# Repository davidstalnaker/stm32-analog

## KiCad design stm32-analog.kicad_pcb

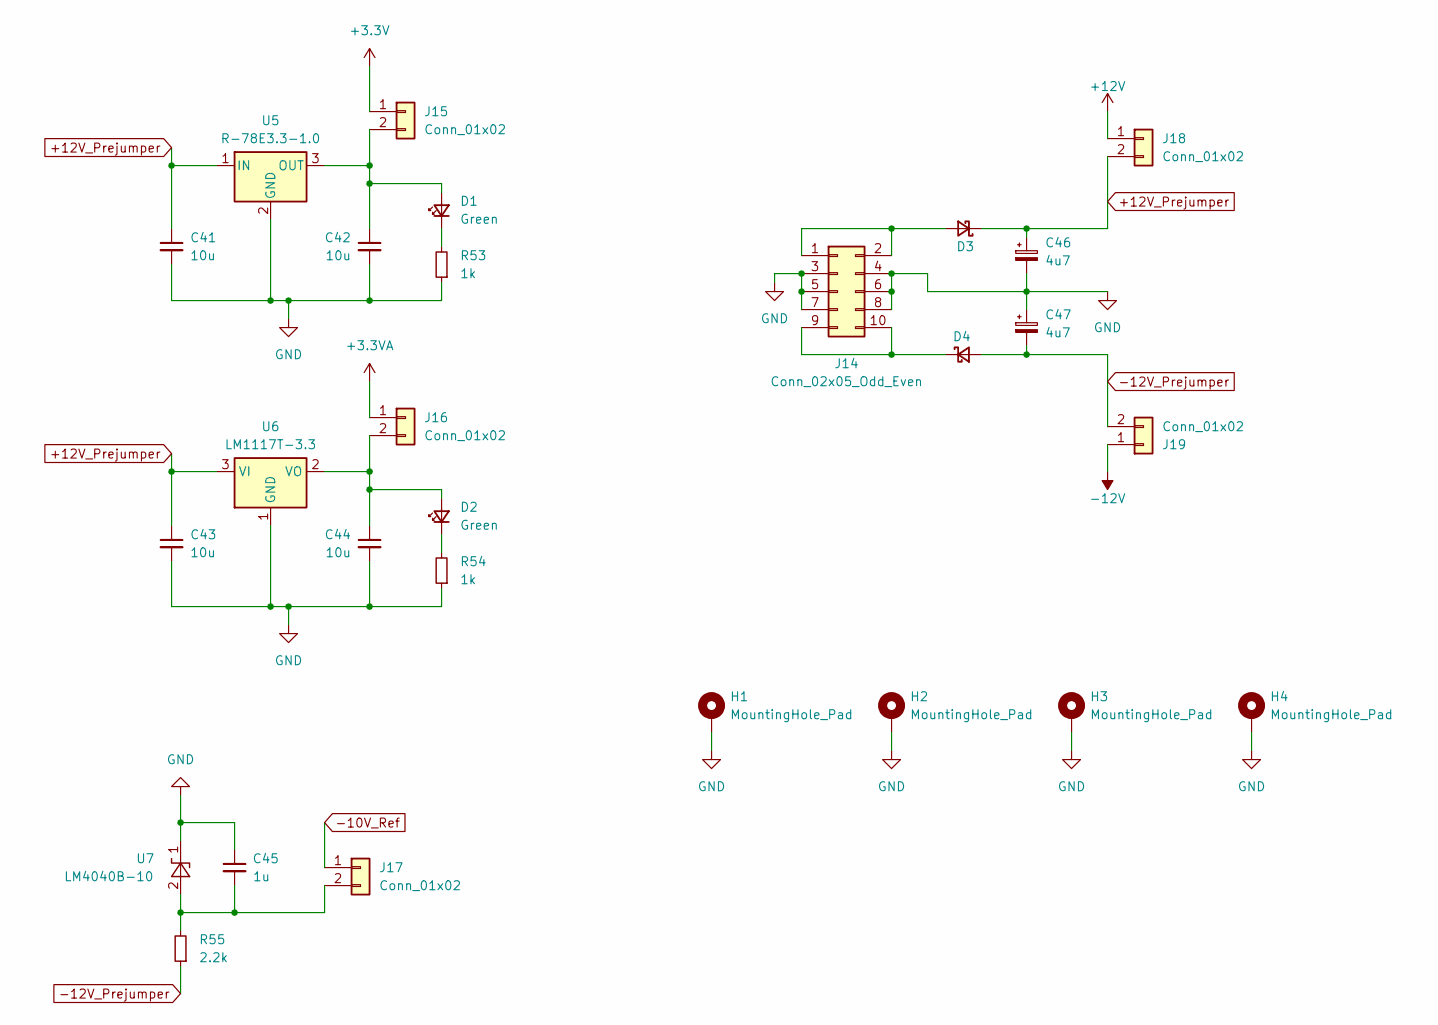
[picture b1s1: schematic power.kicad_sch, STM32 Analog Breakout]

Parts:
C41, C42, C43, C44: 10u; C_0805_2012Metric_Pad1.18x1.45mm_HandSolder
C45: 1u; C_0805_2012Metric_Pad1.18x1.45mm_HandSolder
C46, C47: 4u7; CP_Elec_4x3
D1, D2: Green; LED_0805_2012Metric_Pad1.15x1.40mm_HandSolder
D3, D4: D_Schottky_Small; D_SOD-323_HandSoldering
H1, H2, H3, H4: MountingHole_Pad; MountingHole_3.2mm_M3_DIN965_Pad
J14: Conn_02x05_Odd_Even; PinSocket_2x05_P2.54mm_Vertical
J15, J16, J17, J18, J19: Conn_01x02; PinSocket_1x02_P2.54mm_Vertical
R53, R54: 1k; R_0805_2012Metric_Pad1.20x1.40mm_HandSolder
R55: 2.2k; R_0805_2012Metric_Pad1.20x1.40mm_HandSolder
U5: R-78E3.3-1.0; Converter_DCDC_RECOM_R-78E-0.5_THT
U6: LM1117T-3.3; TO-220-3_Vertical
U7: LM4040B-10; SOT-23

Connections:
+3.3V: J15.1; also elsewhere on the board
+3.3VA: J16.1; also elsewhere on the board
+12V: J18.1; also elsewhere on the board
+12V_Prejumper: C41.1, C43.1, C46.1, D3.1 (K), J18.2, U5.1 (IN), U6.3 (VI)
-10V_Ref: J17.1; also elsewhere on the board
-12V: J19.1; also elsewhere on the board
-12V_Prejumper: C47.2, D4.2 (A), J19.2, R55.1
GND: C41.2, C42.2, C43.2, C44.2, C45.1, C46.2, C47.1, H1.1, H2.1, H3.1, H4.1, J14.3, J14.4, J14.5, J14.6, J14.7, J14.8, R53.1, R54.1, U5.2 (GND), U6.1 (GND), U7.1 (K); also elsewhere on the board
unnamed: C42.1, D1.2 (A), J15.2, U5.3 (OUT)
unnamed: D1.1 (K), R53.2
unnamed: C44.1, D2.2 (A), J16.2, U6.2 (VO)
unnamed: D2.1 (K), R54.2
unnamed: D3.2 (A), J14.1, J14.2
unnamed: D4.1 (K), J14.9, J14.10
unnamed: C45.2, J17.2, R55.2, U7.2 (A)

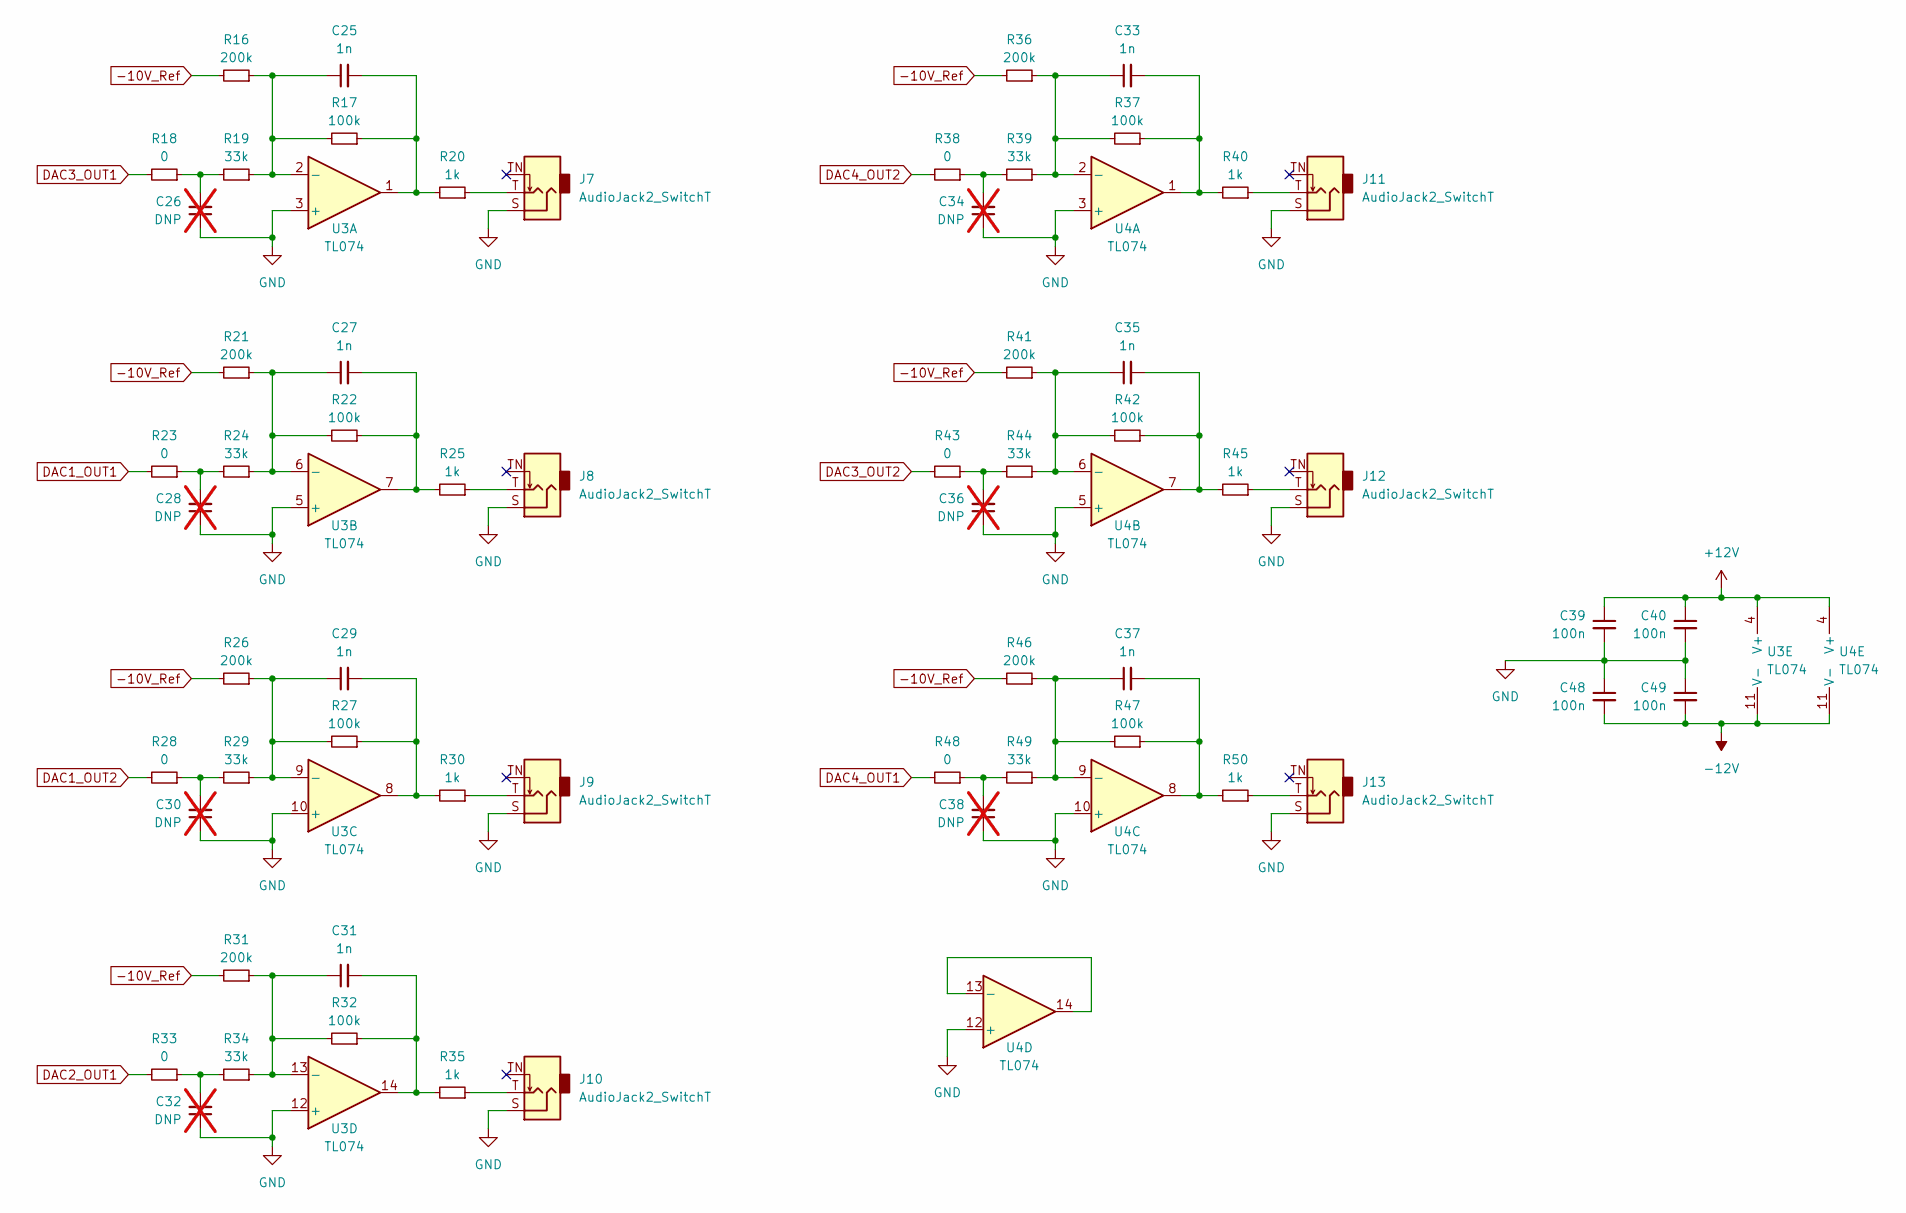
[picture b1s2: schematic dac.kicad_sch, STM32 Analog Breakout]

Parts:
C25, C27, C29, C31, C33, C35, C37: 1n; C_0805_2012Metric_Pad1.18x1.45mm_HandSolder
C26, C28, C30, C32, C34, C36, C38: DNP; C_0805_2012Metric_Pad1.18x1.45mm_HandSolder; not fitted
C39, C40, C48, C49: 100n; C_0805_2012Metric_Pad1.18x1.45mm_HandSolder
J7, J8, J9, J10, J11, J12, J13: AudioJack2_SwitchT; Jack_3.5mm_Thonkiconn_Tight
R16, R21, R26, R31, R36, R41, R46: 200k; R_0805_2012Metric_Pad1.20x1.40mm_HandSolder
R17, R22, R27, R32, R37, R42, R47: 100k; R_0805_2012Metric_Pad1.20x1.40mm_HandSolder
R18, R23, R28, R33, R38, R43, R48: 0; R_0805_2012Metric_Pad1.20x1.40mm_HandSolder
R19, R24, R29, R34, R39, R44, R49: 33k; R_0805_2012Metric_Pad1.20x1.40mm_HandSolder
R20, R25, R30, R35, R40, R45, R50: 1k; R_0805_2012Metric_Pad1.20x1.40mm_HandSolder
U3, U4: TL074; SOIC-14_3.9x8.7mm_P1.27mm

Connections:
+12V: C39.1, C40.1, U3.4 (V+), U4.4 (V+); also elsewhere on the board
-10V_Ref: R16.2, R21.2, R26.2, R31.2, R36.2, R41.2, R46.2; also elsewhere on the board
-12V: C48.2, C49.2, U3.11 (V-), U4.11 (V-); also elsewhere on the board
DAC1_OUT1: R23.2; also elsewhere on the board
DAC1_OUT2: R28.2; also elsewhere on the board
DAC2_OUT1: R33.2; also elsewhere on the board
DAC3_OUT1: R18.2; also elsewhere on the board
DAC3_OUT2: R43.2; also elsewhere on the board
DAC4_OUT1: R48.2; also elsewhere on the board
DAC4_OUT2: R38.2; also elsewhere on the board
GND: C26.1, C28.1, C30.1, C32.1, C34.1, C36.1, C38.1, C39.2, C40.2, C48.1, C49.1, J7.S, J8.S, J9.S, J10.S, J11.S, J12.S, J13.S, U3.3 (+), U3.5 (+), U3.10 (+), U3.12 (+), U4.3 (+), U4.5 (+), U4.10 (+), U4.12 (+); also elsewhere on the board
unnamed: C25.2, R17.1, R20.2, U3.1
unnamed: C26.2, R18.1, R19.2
unnamed: C27.2, R22.1, R25.2, U3.7
unnamed: C28.2, R23.1, R24.2
unnamed: C29.2, R27.1, R30.2, U3.8
unnamed: C30.2, R28.1, R29.2
unnamed: C31.2, R32.1, R35.2, U3.14
unnamed: C32.2, R33.1, R34.2
unnamed: C33.2, R37.1, R40.2, U4.1
unnamed: C34.2, R38.1, R39.2
unnamed: C35.2, R42.1, R45.2, U4.7
unnamed: C36.2, R43.1, R44.2
unnamed: C37.2, R47.1, R50.2, U4.8
unnamed: C38.2, R48.1, R49.2
unnamed: J7.T, R20.1
unnamed: J8.T, R25.1
unnamed: J9.T, R30.1
unnamed: J10.T, R35.1
unnamed: J11.T, R40.1
unnamed: J12.T, R45.1
unnamed: J13.T, R50.1
unnamed: C25.1, R16.1, R17.2, R19.1, U3.2 (-)
unnamed: C27.1, R21.1, R22.2, R24.1, U3.6 (-)
unnamed: C29.1, R26.1, R27.2, R29.1, U3.9 (-)
unnamed: C31.1, R31.1, R32.2, R34.1, U3.13 (-)
unnamed: C33.1, R36.1, R37.2, R39.1, U4.2 (-)
unnamed: C35.1, R41.1, R42.2, R44.1, U4.6 (-)
unnamed: C37.1, R46.1, R47.2, R49.1, U4.9 (-)
unnamed: U4.13 (-), U4.14

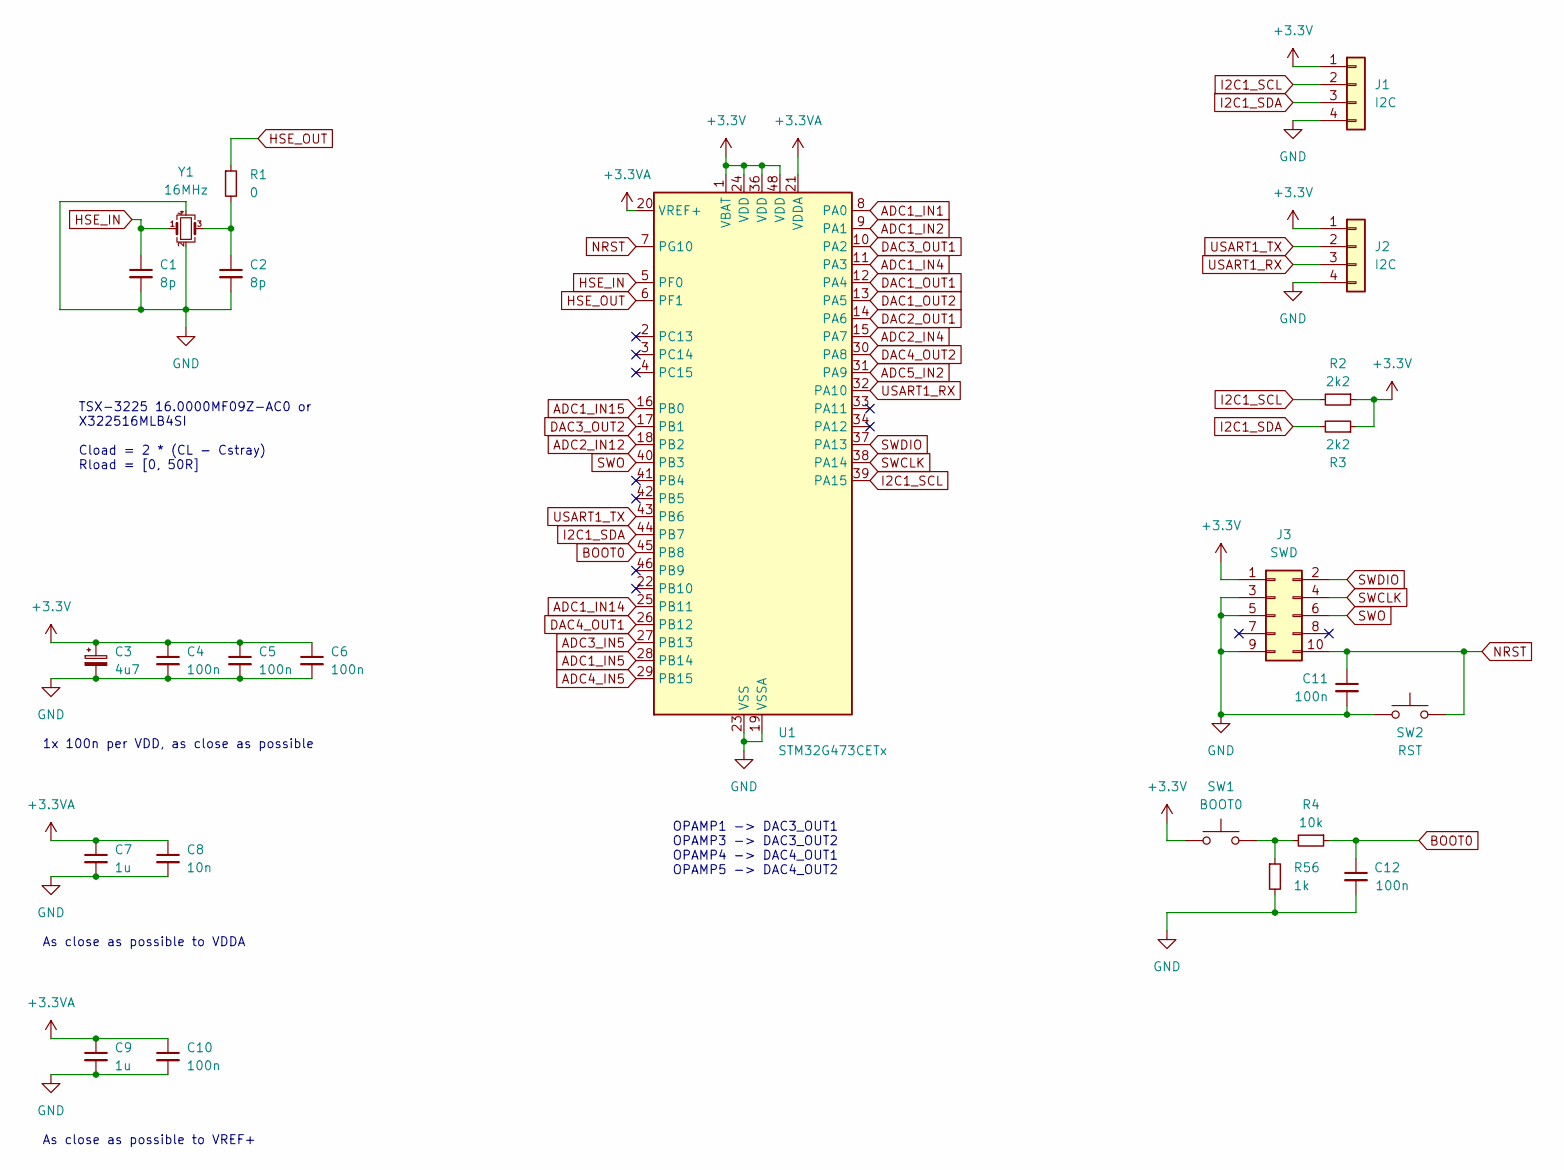
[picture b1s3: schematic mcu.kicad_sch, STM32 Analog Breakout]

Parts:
C1, C2: 8p; C_0805_2012Metric_Pad1.18x1.45mm_HandSolder
C3: 4u7; C_0805_2012Metric_Pad1.18x1.45mm_HandSolder
C4, C5, C6, C10, C11, C12: 100n; C_0805_2012Metric_Pad1.18x1.45mm_HandSolder
C7, C9: 1u; C_0805_2012Metric_Pad1.18x1.45mm_HandSolder
C8: 10n; C_0805_2012Metric_Pad1.18x1.45mm_HandSolder
J1, J2: I2C; PinHeader_1x04_P2.54mm_Vertical
J3: SWD; PinHeader_2x05_P1.27mm_Vertical_SMD
R1: 0; R_0805_2012Metric_Pad1.20x1.40mm_HandSolder
R2, R3: 2k2; R_0805_2012Metric_Pad1.20x1.40mm_HandSolder
R4: 10k; R_0805_2012Metric_Pad1.20x1.40mm_HandSolder
R56: 1k; R_0805_2012Metric_Pad1.20x1.40mm_HandSolder
SW1: BOOT0; SW_Push_1P1T_NO_6x6mm_H9.5mm; Part Number PTS645
SW2: RST; SW_Push_1P1T_NO_6x6mm_H9.5mm; Part Number PTS645
U1: STM32G473CETx; LQFP-48_7x7mm_P0.5mm
Y1: 16MHz; Crystal_SMD_3225-4Pin_3.2x2.5mm

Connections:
+3.3V: C3.1, C4.1, C5.1, C6.1, J1.1, J2.1, J3.1, R2.1, R3.1, SW1.1, U1.1 (VBAT), U1.24 (VDD), U1.36 (VDD), U1.48 (VDD); also elsewhere on the board
+3.3VA: C7.1, C8.1, C9.1, C10.1, U1.20 (VREF+), U1.21 (VDDA); also elsewhere on the board
ADC1_IN1: U1.8 (PA0); also elsewhere on the board
ADC1_IN2: U1.9 (PA1); also elsewhere on the board
ADC1_IN4: U1.11 (PA3); also elsewhere on the board
ADC1_IN5: U1.28 (PB14); also elsewhere on the board
ADC1_IN14: U1.25 (PB11); also elsewhere on the board
ADC1_IN15: U1.16 (PB0); also elsewhere on the board
ADC2_IN4: U1.15 (PA7); also elsewhere on the board
ADC2_IN12: U1.18 (PB2); also elsewhere on the board
ADC3_IN5: U1.27 (PB13); also elsewhere on the board
ADC4_IN5: U1.29 (PB15); also elsewhere on the board
ADC5_IN2: U1.31 (PA9); also elsewhere on the board
BOOT0: C12.1, R4.1, U1.45 (PB8)
DAC1_OUT1: U1.12 (PA4); also elsewhere on the board
DAC1_OUT2: U1.13 (PA5); also elsewhere on the board
DAC2_OUT1: U1.14 (PA6); also elsewhere on the board
DAC3_OUT1: U1.10 (PA2); also elsewhere on the board
DAC3_OUT2: U1.17 (PB1); also elsewhere on the board
DAC4_OUT1: U1.26 (PB12); also elsewhere on the board
DAC4_OUT2: U1.30 (PA8); also elsewhere on the board
GND: C1.2, C2.2, C3.2, C4.2, C5.2, C6.2, C7.2, C8.2, C9.2, C10.2, C11.2, C12.2, J1.4, J2.4, J3.3, J3.5, J3.9, R56.2, SW2.1, U1.19 (VSSA), U1.23 (VSS), U1.35 (VSS), U1.47 (VSS), Y1.2, Y1.4; also elsewhere on the board
HSE_IN: C1.1, U1.5 (PF0), Y1.1
HSE_OUT: R1.1, U1.6 (PF1)
I2C1_SCL: J1.2, R2.2, U1.39 (PA15)
I2C1_SDA: J1.3, R3.2, U1.44 (PB7)
NRST: C11.1, J3.10, SW2.2, U1.7 (PG10)
unnamed: C2.1, R1.2, Y1.3
unnamed: R4.2, R56.1, SW1.2
SWCLK: J3.4, U1.38 (PA14)
SWDIO: J3.2, U1.37 (PA13)
SWO: J3.6, U1.40 (PB3)
USART1_RX: J2.3, U1.32 (PA10)
USART1_TX: J2.2, U1.43 (PB6)

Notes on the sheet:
OPAMP1 -> DAC3_OUT1 OPAMP3 -> DAC3_OUT2 OPAMP4 -> DAC4_OUT1 OPAMP5 -> DAC4_OUT2
As close as possible to VDDA
1x 100n per VDD, as close as possible
TSX-3225 16.0000MF09Z-AC0 or X322516MLB4SI Cload = 2 * (CL - Cstray) Rload = [0, 50R]
As close as possible to VREF+

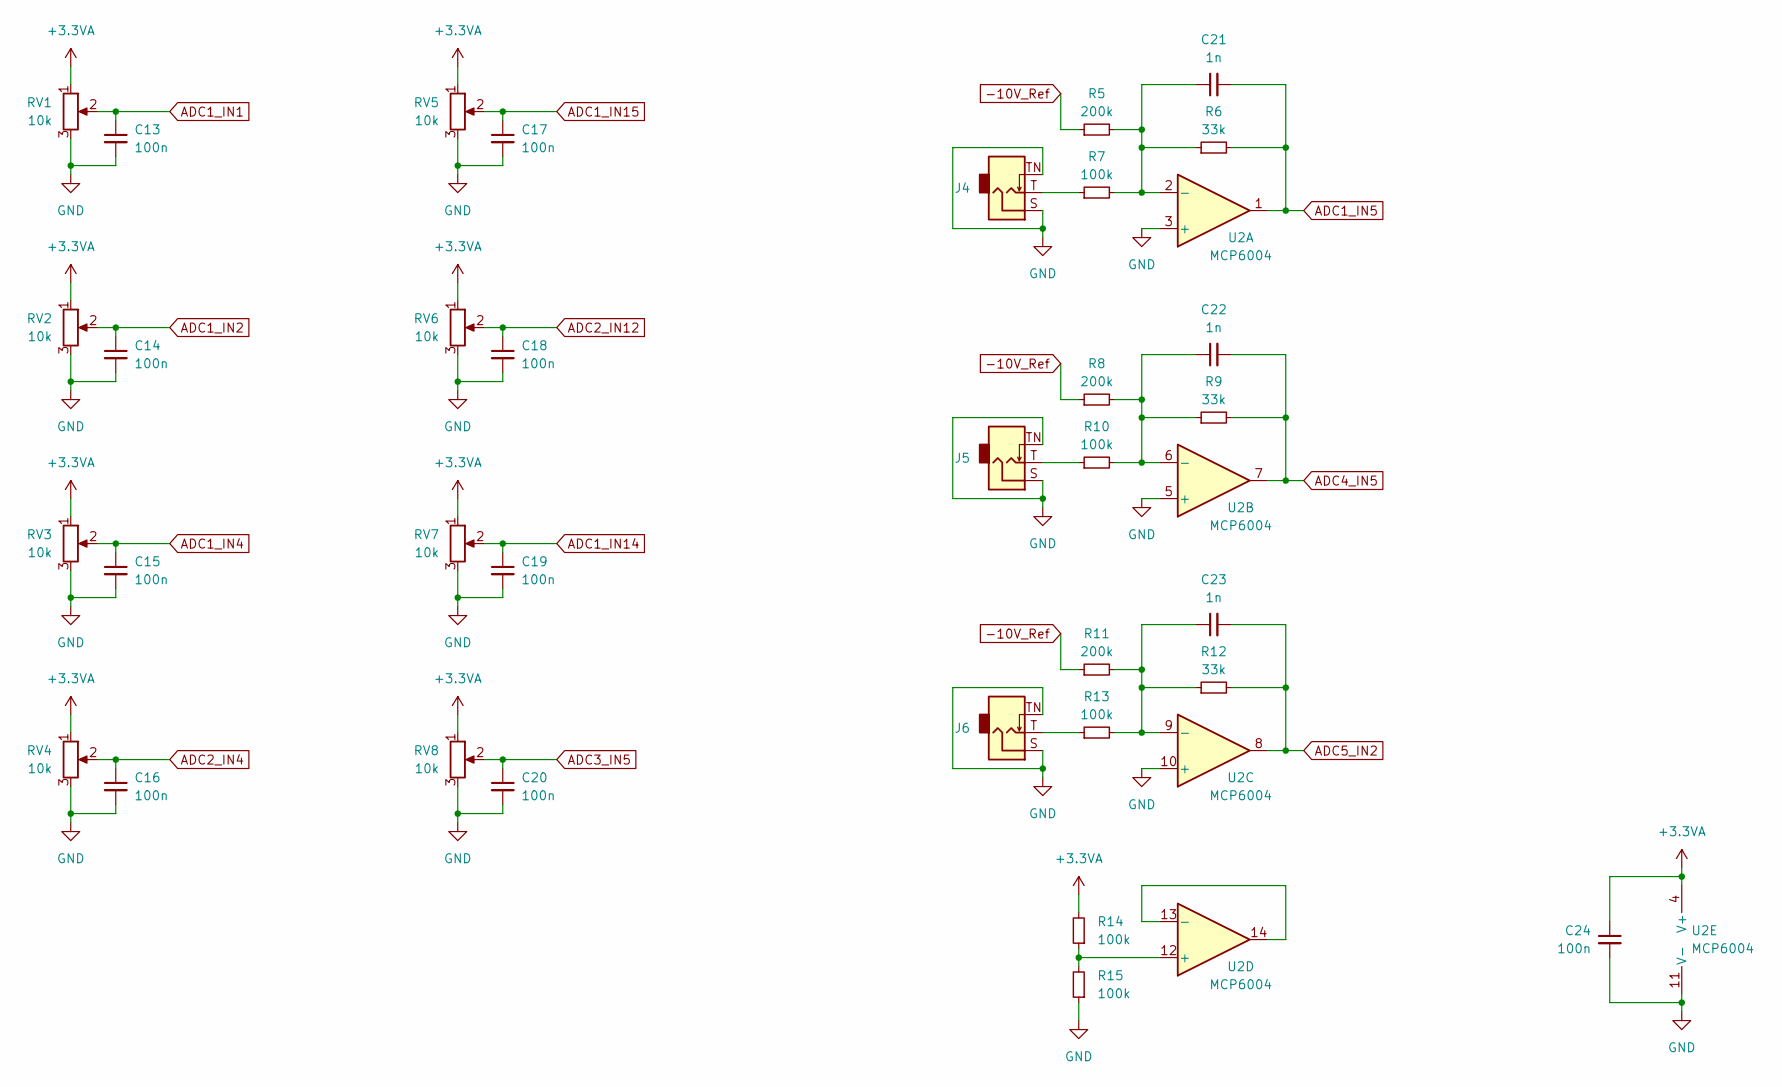
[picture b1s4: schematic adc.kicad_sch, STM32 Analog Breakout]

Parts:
C13, C14, C15, C16, C17, C18, C19, C20, C24: 100n; C_0805_2012Metric_Pad1.18x1.45mm_HandSolder
C21, C22, C23: 1n; C_0805_2012Metric_Pad1.18x1.45mm_HandSolder
J4, J5, J6: AudioJack2_SwitchT; Jack_3.5mm_Thonkiconn_Tight
R5, R8, R11: 200k; R_0805_2012Metric_Pad1.20x1.40mm_HandSolder
R6, R9, R12: 33k; R_0805_2012Metric_Pad1.20x1.40mm_HandSolder
R7, R10, R13, R14, R15: 100k; R_0805_2012Metric_Pad1.20x1.40mm_HandSolder
RV1, RV2, RV3, RV4, RV5, RV6, RV7, RV8: 10k; Potentiometer_Alpha_RD901F-40-00D_Single_Vertical
U2: MCP6004; SOIC-14_3.9x8.7mm_P1.27mm

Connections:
+3.3VA: C24.1, R14.2, RV1.1, RV2.1, RV3.1, RV4.1, RV5.1, RV6.1, RV7.1, RV8.1, U2.4 (V+); also elsewhere on the board
-10V_Ref: R5.1, R8.1, R11.1; also elsewhere on the board
ADC1_IN1: C13.1, RV1.2; also elsewhere on the board
ADC1_IN2: C14.1, RV2.2; also elsewhere on the board
ADC1_IN4: C15.1, RV3.2; also elsewhere on the board
ADC1_IN5: C21.2, R6.2, U2.1; also elsewhere on the board
ADC1_IN14: C19.1, RV7.2; also elsewhere on the board
ADC1_IN15: C17.1, RV5.2; also elsewhere on the board
ADC2_IN4: C16.1, RV4.2; also elsewhere on the board
ADC2_IN12: C18.1, RV6.2; also elsewhere on the board
ADC3_IN5: C20.1, RV8.2; also elsewhere on the board
ADC4_IN5: C22.2, R9.2, U2.7; also elsewhere on the board
ADC5_IN2: C23.2, R12.2, U2.8; also elsewhere on the board
GND: C13.2, C14.2, C15.2, C16.2, C17.2, C18.2, C19.2, C20.2, C24.2, J4.S, J4.TN, J5.S, J5.TN, J6.S, J6.TN, R15.1, RV1.3, RV2.3, RV3.3, RV4.3, RV5.3, RV6.3, RV7.3, RV8.3, U2.3 (+), U2.5 (+), U2.10 (+), U2.11 (V-); also elsewhere on the board
unnamed: J4.T, R7.1
unnamed: J5.T, R10.1
unnamed: J6.T, R13.1
unnamed: C21.1, R5.2, R6.1, R7.2, U2.2 (-)
unnamed: C22.1, R8.2, R9.1, R10.2, U2.6 (-)
unnamed: C23.1, R11.2, R12.1, R13.2, U2.9 (-)
unnamed: R14.1, R15.2, U2.12 (+)
unnamed: U2.13 (-), U2.14

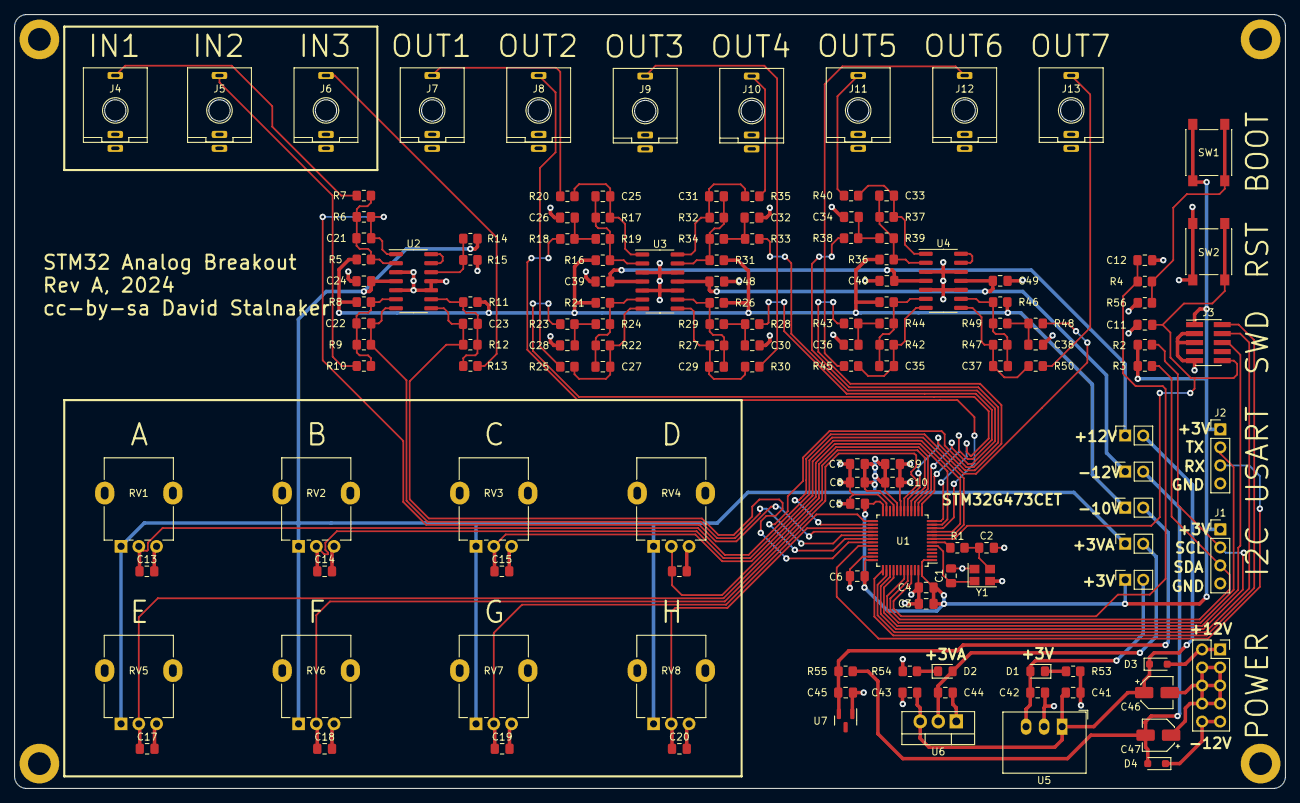
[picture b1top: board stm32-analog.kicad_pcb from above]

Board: 4 copper layers, 179.0 x 109.0 mm, 148 parts (0 on the bottom side), 83 nets.

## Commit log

2024-01-05 Initial schematic.
2024-01-18 Added initial layout.
2024-01-18 Renamed files.
2024-01-20 Add kibot automation.
2024-01-20 Fix mounting holes.

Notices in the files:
stm32-analog.kicad_pcb:
cc-by-sa David Stalnaker
